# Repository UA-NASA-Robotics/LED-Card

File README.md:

# LED-Card
LED Card for the 2020-21 bot

## Design Specs

Interfaces with LED buffers for neopixels

Flash different statuses (listed below)

## CAN Bus information

### Status Lights
Red/Blue: Not connected

Green: Connected in Manual mode

Purple: Connected in Autonomous mode

### Planned features
Scrolling colors (flashy)

Digging mode colors

More Statuses

Overall more awesomeness

### Overview / Notes
#### dsPIC33EP512GM604

#### System:
24MHz clock rate for chip

##### PLL:
1:30 Prescaler (800kHz)

1:150 FeedBack (120MHz)

1:2 Postscaler (60MHz)

60MHz Fosc

30MHz Fosc/2

##### Watchdog:

Non-Window Mode

1:128 Prescaler

1:32768 Postscaler

128s Timeout

##### DMA:

###### CH0

Continuous Transfer, No Ping-Pong

Triggered on CAN1RX

16bit datasize

0x7 Transfer Count

###### CH1

Continuous Transfer, No Ping-Pong

Triggered on CAN1TX

16bit datasize

0x7 Transfer Count

#### CAN 1 
500kbps
15 quanta

80% sample

Sync,Prop,Phase,Phase
1,3,8,3

CAN Interrupt enabled

DMA Buffer Size 32

2 Transmit Buffers

Message ID 0x100
SID
Filter 0
Mask 0
Rx RB2

Msg ID 0x7c0
SID
Filter 1
Mask 1
Rx RB3

#### CAN 1 
20kbps
15 quanta

80% sample

Sync,Prop,Phase,Phase
1,3,8,3

DMA Buffer Size 32

1 Transmit Buffer

Message ID 0x100
SID
Filter 0
Mask 0
Rx RB2

Msg ID 0x7c0
SID
Filter 1
Mask 1
Rx RB3

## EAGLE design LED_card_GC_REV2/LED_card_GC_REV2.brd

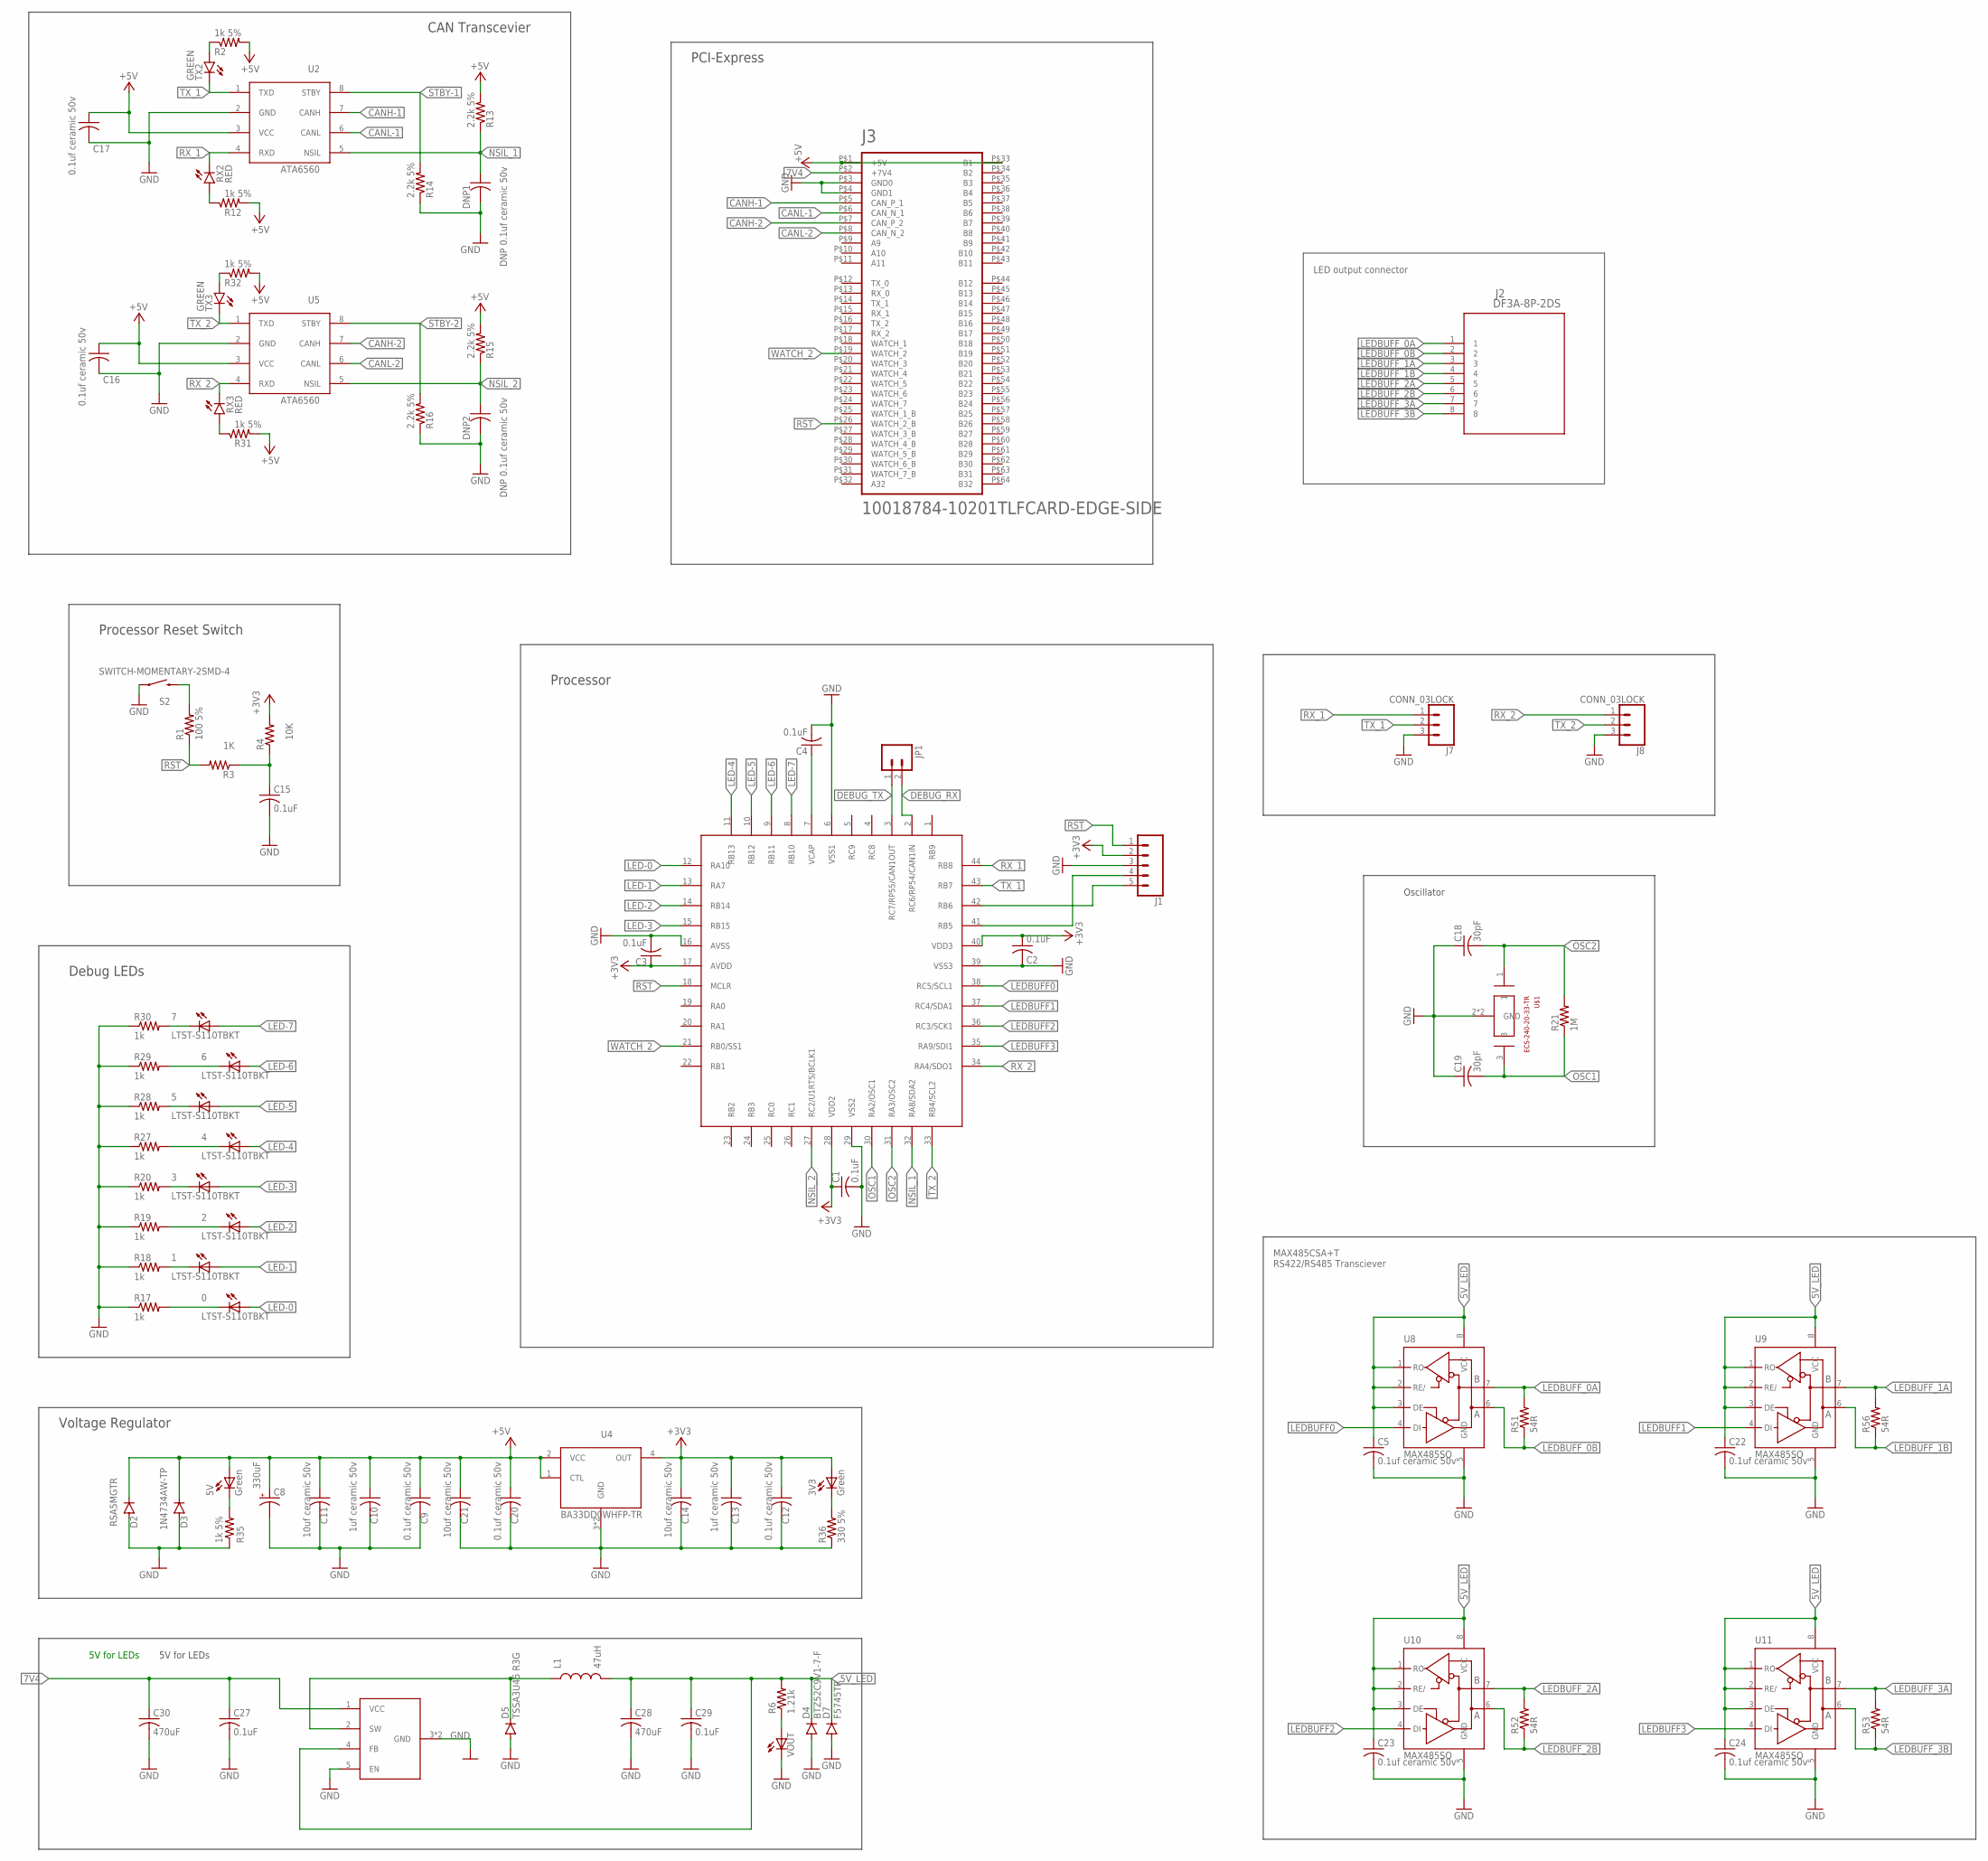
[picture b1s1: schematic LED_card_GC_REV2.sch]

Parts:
0, 1, 2, 3, 4, 5, 6, 7: LTST-S110TBKT; LED-90
3V3, 5V: Green; LED-90
C1, C2, C3, C4, C15: 0.1uF; C0805
C5, C9, C12, C16, C17, C20, C22, C23, C24: 0.1uf ceramic 50v; C0805
C8: 330uF; 140CLH-1014
C10, C13: 1uf ceramic 50v; C0805
C11, C14, C21: 10uf ceramic 50v; C0805
C18, C19: 30pF; C0805
C27, C29: 0.1uF; C1825
C28, C30: 470uF; C1825
D2: RSA5MGTR; SOD123
D3: 1N4734AW-TP; SOD123
D4: BTZ52C9V1-7-F; SOD123
D5: TSSA3U45 R3G; DO214AC
D7: F5745TR; SOD123
DNP1, DNP2: DNP 0.1uf ceramic 50v; C0805
J1: CONN_05LOCK; 1X05_LOCK
J2: DF3A-8P-2DS; CON8_1X8_R_DF3
J3: 10018784-10201TLFCARD-EDGE-SIDE; CARDEDGE_SIDE
J7, J8: CONN_03LOCK; 1X03_LOCK
JP1: CONN_02PTH; 1X02
L1: 47uH; 0805
R1: 100 5%; R0805
R2, R12, R31, R32, R35: 1k 5%; R0805
R3: 1K; R0805
R4: 10K; R0805
R6: 1.21k; R0805
R13, R14, R15, R16: 2.2k 5%; R0805
R17, R18, R19, R20, R27, R28, R29, R30: 1k; R0805
R21: 1M; R0805
R36: 330 5%; R0805
R51, R52, R53, R56: 54R; 0805
RX2, RX3: RED; CHIP-LED0805
S2: SWITCH-MOMENTARY-2SMD-4; TACTILE_SWITCH_TALL
TX2, TX3: GREEN; CHIP-LED0805
U2, U5: ATA6560; SO08
U3: DSPIC33EP512GM604; TQFP-44
U4: BA33DD0WHFP-TR; HRP5
U8, U9, U10, U11: MAX485SO; SO08
U$1: ECS-240-20-33-TR; ECX-32
U$3: TS2596CM550; HRP5
VOUT1: VOUT; CHIP-LED0805

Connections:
5V_LED: C5.1, C22.1, C23.1, C24.1, C28.1, C29.1, D4.C, D7.C, L1.2, R6.2, U8.1 (RO), U8.2 (RE/), U8.3 (DE), U8.8 (VCC), U9.1 (RO), U9.2 (RE/), U9.3 (DE), U9.8 (VCC), U10.1 (RO), U10.2 (RE/), U10.3 (DE), U10.8 (VCC), U11.1 (RO), U11.2 (RE/), U11.3 (DE), U11.8 (VCC), U$3.4 (FB)
7V4: C27.1, C30.1, J3.P$2 (+7V4), U$3.1 (VCC)
+3V3: 3V3.+ (A+), C1.1, C2.1, C3.1, C12.1, C13.1, C14.1, J1.2, R4.2, U3.17 (AVDD), U3.28 (VDD2), U3.40 (VDD3), U4.4 (OUT)
+5V: 5V.+ (A+), C8.+, C9.1, C10.1, C11.1, C16.1, C17.1, C20.1, C21.1, D2.C, D3.C, J3.P$1 (+5V), J3.P$33 (B1), R2.2, R12.2, R13.2, R15.2, R31.2, R32.2, U2.3 (VCC), U4.1 (CTL), U4.2 (VCC), U5.3 (VCC)
CANH-1: J3.P$5 (CAN_P_1), U2.7 (CANH)
CANH-2: J3.P$7 (CAN_P_2), U5.7 (CANH)
CANL-1: J3.P$6 (CAN_N_1), U2.6 (CANL)
CANL-2: J3.P$8 (CAN_N_2), U5.6 (CANL)
DEBUG_RX: JP1.2, U3.2 (RC6/RP54/CAN1IN)
DEBUG_TX: JP1.1, U3.3 (RC7/RP55/CAN1OUT)
GND: C1.2, C2.2, C3.2, C4.2, C5.2, C8.-, C9.2, C10.2, C11.2, C12.2, C13.2, C14.2, C15.2, C16.2, C17.2, C18.1, C19.1, C20.2, C21.2, C22.2, C23.2, C24.2, C27.2, C28.2, C29.2, C30.2, D2.A, D3.A, D4.A, D5.A, D7.A, DNP1.2, DNP2.2, J1.3, J3.P$3 (GND0), J3.P$4 (GND1), J7.3, J8.3, R14.1, R16.1, R17.1, R18.1, R19.1, R20.1, R27.1, R28.1, R29.1, R30.1, R35.1, R36.1, S2.A2 (1), U2.2 (GND), U3.6 (VSS1), U3.16 (AVSS), U3.29 (VSS2), U3.39 (VSS3), U4.3 (GND), U4.G (GND), U5.2 (GND), U8.5 (GND), U9.5 (GND), U10.5 (GND), U11.5 (GND), U$1.2 (GND), U$1.4 (GND), U$3.3 (GND), U$3.5 (EN), U$3.G (GND), VOUT1.C
LED-0: 0.+ (A+), U3.12 (RA10)
LED-1: 1.+ (A+), U3.13 (RA7)
LED-2: 2.+ (A+), U3.14 (RB14)
LED-3: 3.+ (A+), U3.15 (RB15)
LED-4: 4.+ (A+), U3.11 (RB13)
LED-5: 5.+ (A+), U3.10 (RB12)
LED-6: 6.+ (A+), U3.9 (RB11)
LED-7: 7.+ (A+), U3.8 (RB10)
LEDBUFF0: U3.38 (RC5/SCL1), U8.4 (DI)
LEDBUFF1: U3.37 (RC4/SDA1), U9.4 (DI)
LEDBUFF2: U3.36 (RC3/SCK1), U10.4 (DI)
LEDBUFF3: U3.35 (RA9/SDI1), U11.4 (DI)
LEDBUFF_0A: J2.1, R51.2, U8.7 (B)
LEDBUFF_0B: J2.2, R51.1, U8.6 (A)
LEDBUFF_1A: J2.3, R56.2, U9.7 (B)
LEDBUFF_1B: J2.4, R56.1, U9.6 (A)
LEDBUFF_2A: J2.5, R52.2, U10.7 (B)
LEDBUFF_2B: J2.6, R52.1, U10.6 (A)
LEDBUFF_3A: J2.7, R53.2, U11.7 (B)
LEDBUFF_3B: J2.8, R53.1, U11.6 (A)
unnamed: C15.1, R3.1, R4.1
unnamed: R1.2, S2.B2 (2)
unnamed: 5V.- (C-), R35.2
unnamed: 3V3.- (C-), R36.2
unnamed: J1.5, U3.42 (RB6)
unnamed: 6.- (C-), R29.2
unnamed: D5.C, L1.1, U$3.2 (SW)
unnamed: R6.1, VOUT1.A
unnamed: 7.- (C-), R30.2
unnamed: J1.4, U3.41 (RB5)
unnamed: C4.1, U3.7 (VCAP)
unnamed: 5.- (C-), R28.2
unnamed: 4.- (C-), R27.2
unnamed: 3.- (C-), R20.2
unnamed: 2.- (C-), R19.2
unnamed: 1.- (C-), R18.2
unnamed: 0.- (C-), R17.2
unnamed: R12.1, RX2.A
unnamed: R2.1, TX2.A
unnamed: R31.1, RX3.A
unnamed: R32.1, TX3.A
NSIL_1: DNP1.1, R13.1, U2.5 (NSIL), U3.32 (RA8/SDA2)
NSIL_2: DNP2.1, R15.1, U3.27 (RC2/U1RTS/BCLK1), U5.5 (NSIL)
OSC1: C19.2, R21.1, U3.30 (RA2/OSC1), U$1.3
OSC2: C18.2, R21.2, U3.31 (RA3/OSC2), U$1.1
RST: J1.1, J3.P$26 (WATCH_2_B), R1.1, R3.2, U3.18 (MCLR)
RX_1: J7.1, RX2.C, U2.4 (RXD), U3.44 (RB8)
RX_2: J8.1, RX3.C, U3.34 (RA4/SDO1), U5.4 (RXD)
STBY-1: R14.2, U2.8 (STBY)
STBY-2: R16.2, U5.8 (STBY)
TX_1: J7.2, TX2.C, U2.1 (TXD), U3.43 (RB7)
TX_2: J8.2, TX3.C, U3.33 (RB4/SCL2), U5.1 (TXD)
WATCH_2: J3.P$19 (WATCH_2), U3.21 (RB0/SS1)

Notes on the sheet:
Debug LEDs
Processor Reset Switch
Processor
Oscillator
Voltage Regulator
CAN Transcevier
PCI-Express
5V for LEDs
MAX485CSA+T RS422/RS485 Transciever
LED output connector

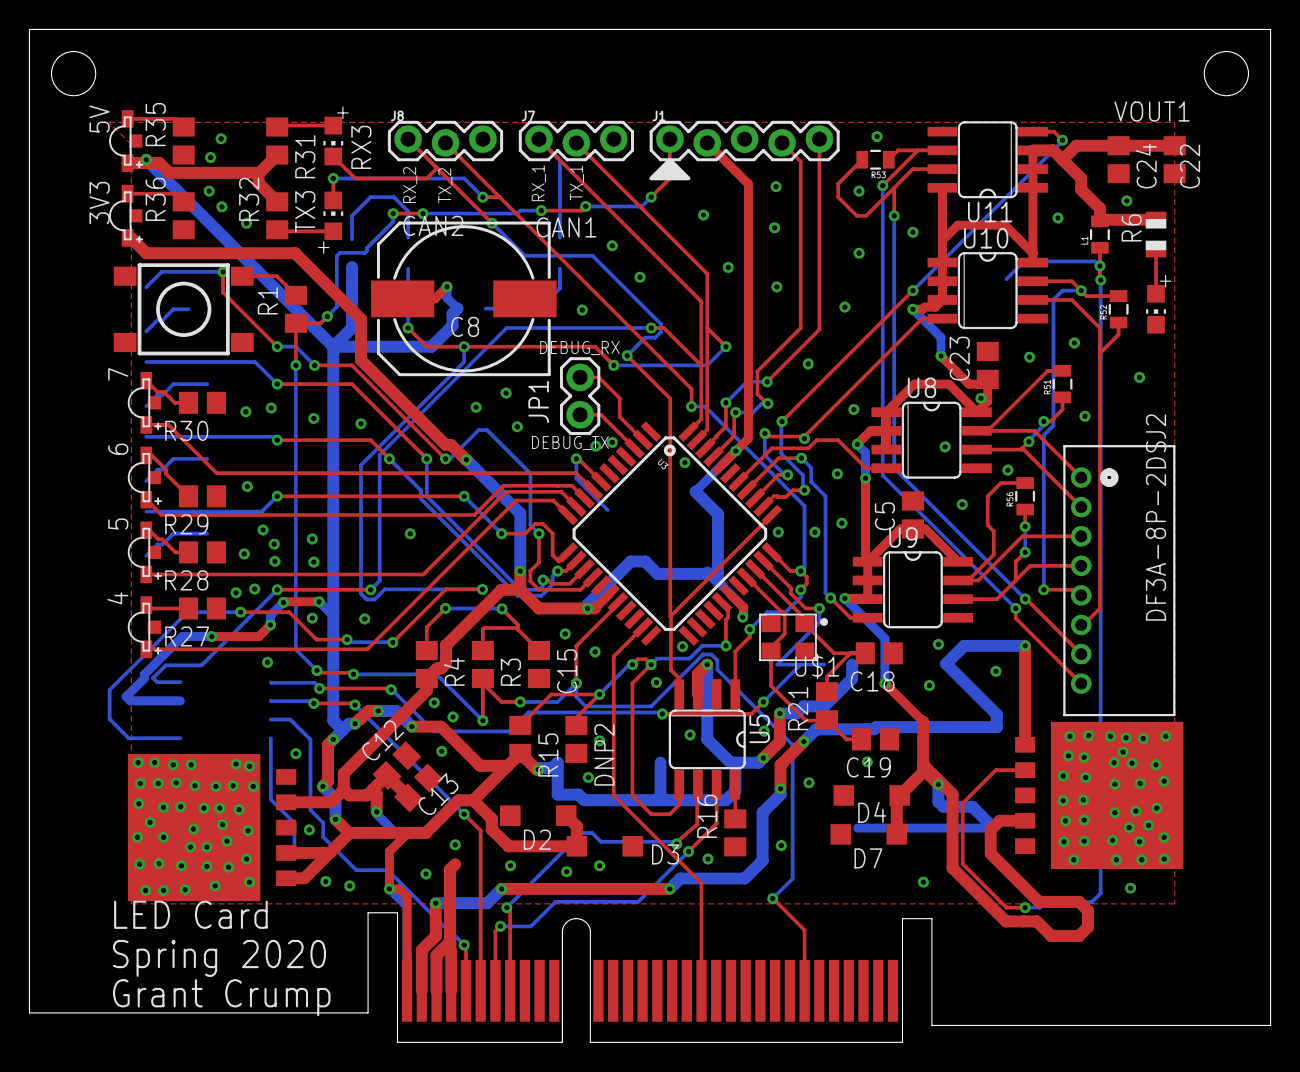
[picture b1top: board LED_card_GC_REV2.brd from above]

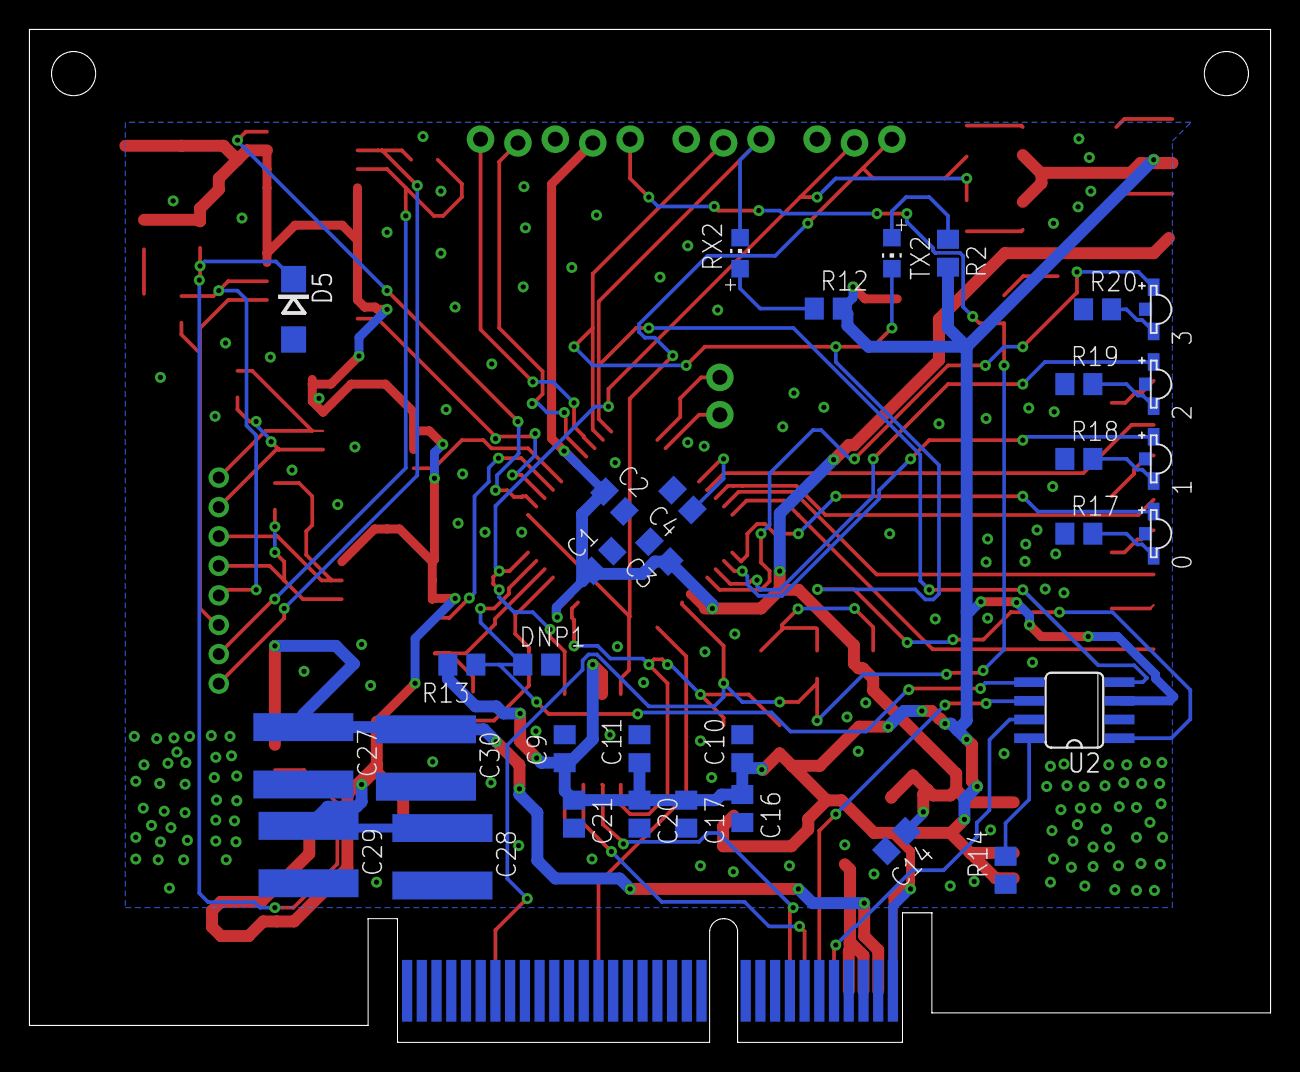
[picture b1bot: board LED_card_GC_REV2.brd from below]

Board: 2 copper layers, 84.3 x 68.8 mm, 93 parts (33 on the bottom side), 64 nets.

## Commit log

2020-09-08 Added EAGLE files
2020-09-09 Added .gitignore
    ignore CAMoutputs and old router/LED files
2020-09-09 *actually added gitignore*
2020-09-09 Update README.md
    fixed line breaks
2020-09-16 initial project (MCC config from RouterRefactor) + ReadMe update

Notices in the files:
parts and their libraries:
SparkFun-Resistors: Licensing: Creative Commons ShareAlike 4.0 International - https://creativecommons.org/licenses/by-sa/4.0
SparkFun: Licensing: CC v3.0 Share-Alike You are welcome to use this library for commercial purposes.
